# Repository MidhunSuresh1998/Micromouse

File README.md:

# Micromouse
A micromouse which detects and follows line in a maze and solves it with algorithm

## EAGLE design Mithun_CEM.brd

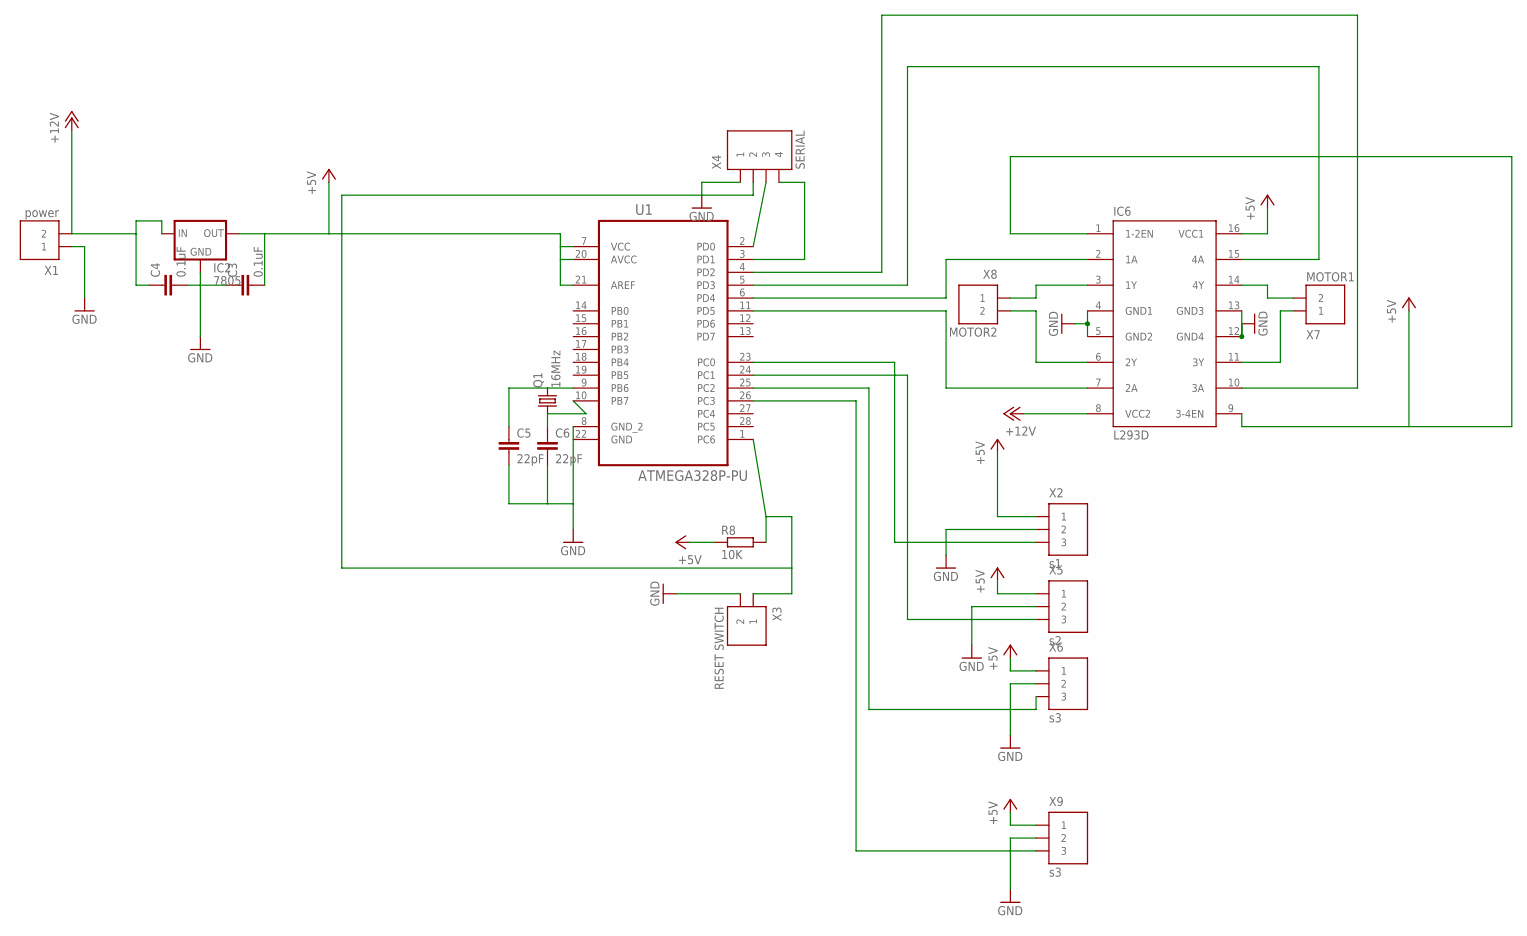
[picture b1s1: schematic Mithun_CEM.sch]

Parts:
C3, C4: 0.1uF; C050-024X044
C5, C6: 22pF; C050-024X044
IC2: 7805; 78MXXS
IC6: L293D; DIL16
Q1: 16MHz; HC18U-V
R8: 10K; 0204/5
U1: ATMEGA328P-PU; DIP254P762X457-28
X1: power; MKS1852-6-0-202
X2: s1; MKS1853-6-0-303
X3: RESET SWITCH; MKS1852-6-0-202
X4: SERIAL; MKS1854-6-0-404
X5: s2; MKS1853-6-0-303
X6, X9: s3; MKS1853-6-0-303
X7: MOTOR1; MKS1852-6-0-202
X8: MOTOR2; MKS1852-6-0-202

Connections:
+5V: C3.2, IC2.OUT, IC6.1 (1-2EN), IC6.9 (3-4EN), IC6.16 (VCC1), R8.1, U1.7 (VCC), U1.20 (AVCC), U1.21 (AREF), X2.1, X5.1, X6.1, X9.1
+12V: C4.1, IC2.IN, IC6.8 (VCC2), X1.2
GND: C3.1, C4.2, C5.2, C6.2, IC2.GND, IC6.4 (GND1), IC6.5 (GND2), IC6.12 (GND4), IC6.13 (GND3), U1.8 (GND_2), U1.22 (GND), X1.1, X2.2, X3.2, X4.1, X5.2, X6.2, X9.2
unnamed: IC6.15 (4A), U1.5 (PD3)
unnamed: U1.23 (PC0), X2.3
unnamed: U1.26 (PC3), X9.3
unnamed: U1.24 (PC1), X5.3
unnamed: U1.25 (PC2), X6.3
unnamed: C5.1, Q1.2, U1.9 (PB6)
unnamed: C6.1, Q1.1, U1.10 (PB7)
unnamed: IC6.2 (1A), U1.6 (PD4)
unnamed: R8.2, U1.1 (PC6), X3.1, X4.2
unnamed: U1.2 (PD0), X4.3
unnamed: U1.3 (PD1), X4.4
unnamed: IC6.10 (3A), U1.4 (PD2)
unnamed: IC6.3 (1Y), X8.1
unnamed: IC6.6 (2Y), X8.2
unnamed: IC6.11 (3Y), X7.1
unnamed: IC6.14 (4Y), X7.2
unnamed: IC6.7 (2A), U1.11 (PD5)

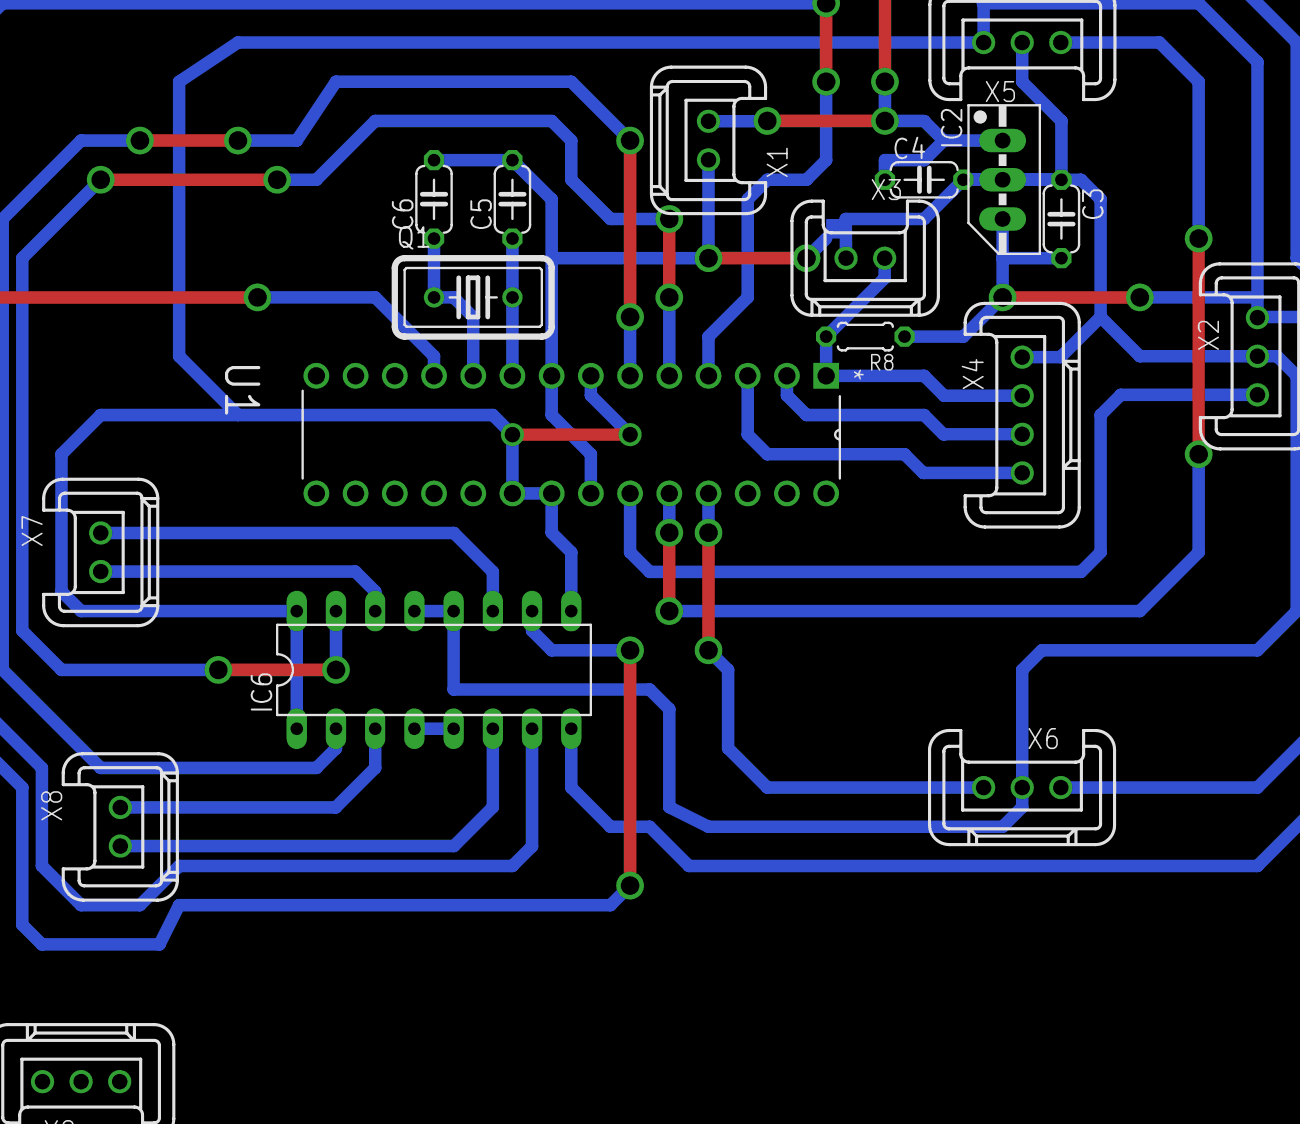
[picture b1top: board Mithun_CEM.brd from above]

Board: 2 copper layers, 18 parts (0 on the bottom side), 20 nets.
